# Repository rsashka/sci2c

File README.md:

# SCI2C
Smart Card I2C protocol implementation

## Specifications
- SCI2C Protocol Specification: https://www.nxp.com/docs/en/supporting-information/AN12207.pdf
- I2C-bus specification and user manual: https://www.nxp.com/docs/en/user-guide/UM10204.pdf
- A7001AG Secure authentication microcontroller http://datasheet.elcodis.com/pdf2/99/92/999291/a7001ag.pdf

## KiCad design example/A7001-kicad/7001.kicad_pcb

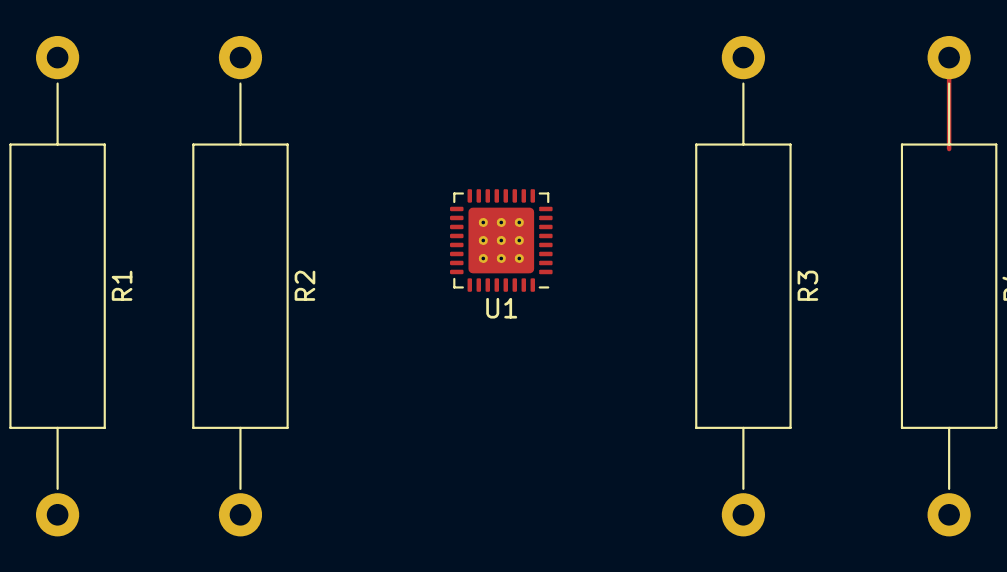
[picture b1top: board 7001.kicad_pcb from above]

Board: 2 copper layers, 5 parts (0 on the bottom side), 6 nets.

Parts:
R1, R2: 4.7K; R_Axial_DIN0516_L15.5mm_D5.0mm_P25.40mm_Horizontal
R3, R4: 10K; R_Axial_DIN0516_L15.5mm_D5.0mm_P25.40mm_Horizontal
U1: A7001AG; QFN-32-1EP_5x5mm_P0.5mm_EP3.65x3.65mm_ThermalVias

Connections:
+3V3: R1.1, R2.1, R3.1, U1.24
GND: R4.2, U1.1
unnamed: R3.2, U1.18
unnamed: R4.1, U1.22
SCL: R1.2, U1.7
SDA: R2.2, U1.5

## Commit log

2019-01-21 Update README.md
    Add spec link
2019-01-24 Add example by arduino and add AUTHORS file.
2019-01-24 Add original apdu files from Android source
2019-01-24 Refactor android apdu files for build by C++11 and make apdu parser header only
2019-01-24 Remove apdu.cpp for implementation header only
2019-01-24 Add NetBeans IDE script for run UnitTest
2019-01-24 Add kicad files for A7001AG microcontroller
2019-01-24 Add datasheet and spec links
2019-01-24 Update README.md
    Fixed markdown format
